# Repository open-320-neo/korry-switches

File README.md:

# Korry Switches

These are multi language docs in PDF form:

[English Documentation](https://korry.open320neo.ch/documentation-en.pdf)
[German Documentation](https://korry.open320neo.ch/README.pdf)

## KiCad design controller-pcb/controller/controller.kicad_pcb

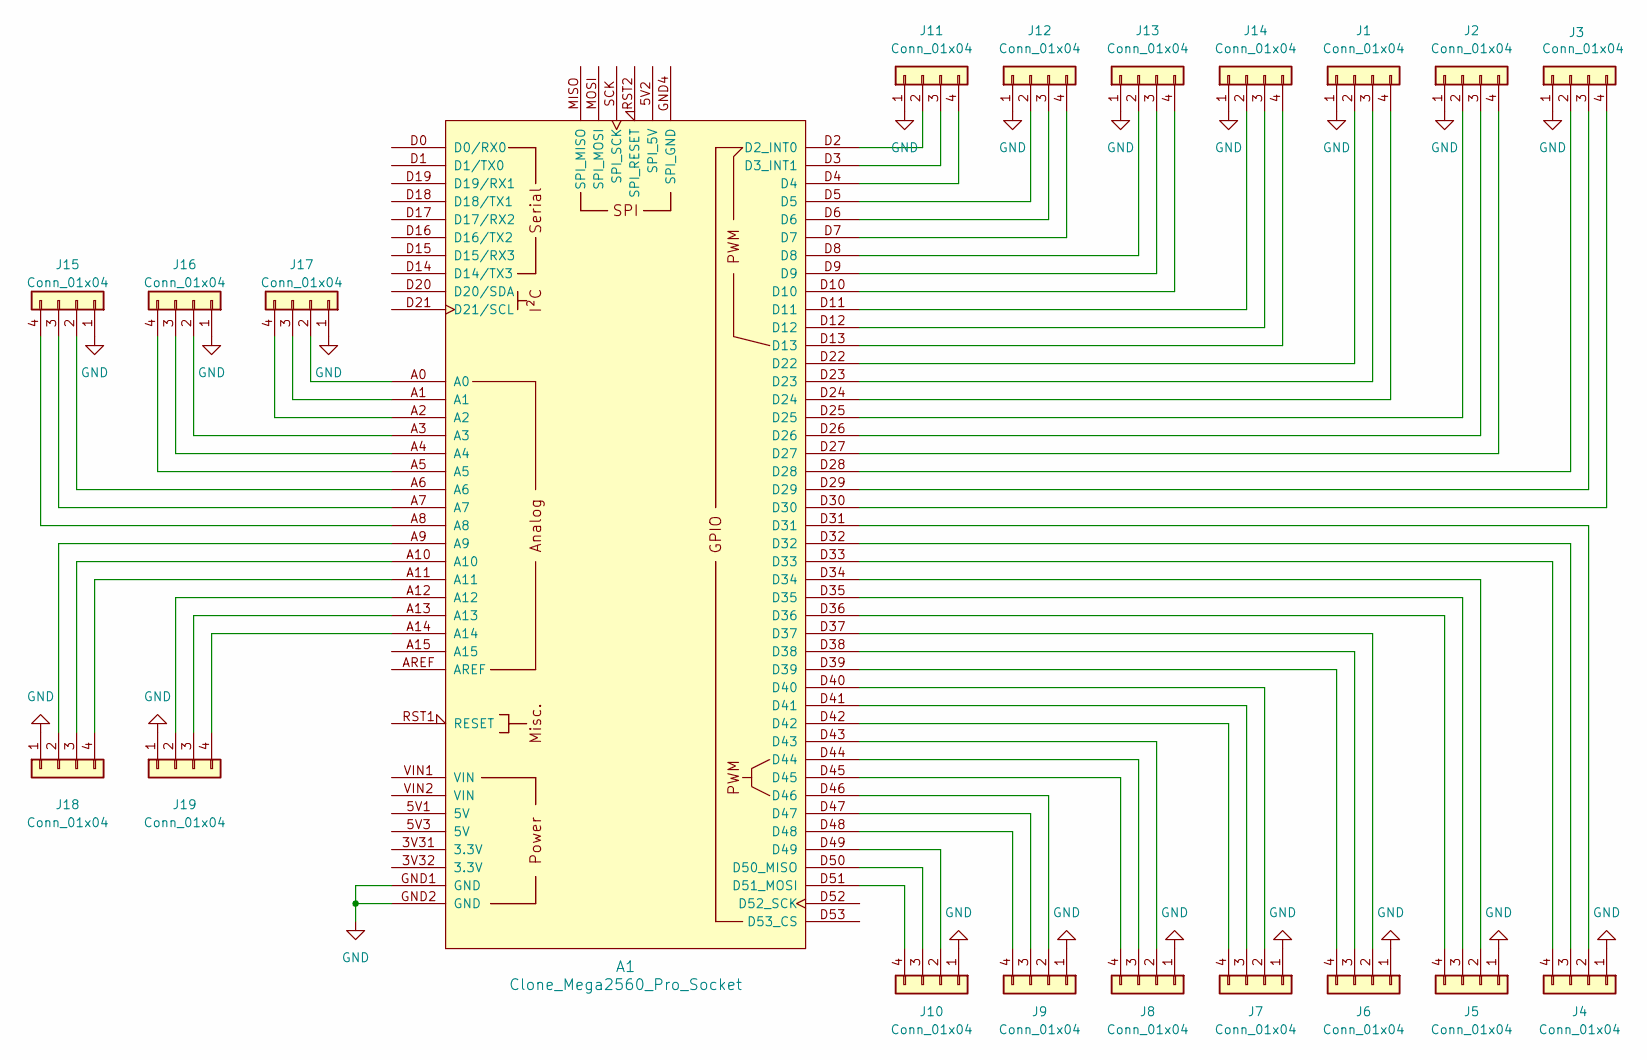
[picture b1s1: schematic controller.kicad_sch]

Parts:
A1: Clone_Mega2560_Pro_Socket
J1, J2, J3, J4, J5, J6, J7, J8, J9, J10, J11, J12, J13, J14, J15, J16, J17, J18, J19: Conn_01x04; JST_ZH_B4B-ZR_1x04_P1.50mm_Vertical

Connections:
GND: A1.GND1 (GND), A1.GND2 (GND), J1.1, J2.1, J3.1, J4.1, J5.1, J6.1, J7.1, J8.1, J9.1, J10.1, J11.1, J12.1, J13.1, J14.1, J15.1, J16.1, J17.1, J18.1, J19.1
unnamed: A1.D2 (D2_INT0), J11.2
unnamed: A1.D3 (D3_INT1), J11.3
unnamed: A1.D50 (D50_MISO), J10.3
unnamed: A1.D51 (D51_MOSI), J10.4
unnamed: A1.D22, J1.2
unnamed: A1.D23, J1.3
unnamed: A1.D24, J1.4
unnamed: A1.D25, J2.2
unnamed: A1.D26, J2.3
unnamed: A1.D27, J2.4
unnamed: A1.D28, J3.2
unnamed: A1.D29, J3.3
unnamed: A1.D30, J3.4
unnamed: A1.D31, J4.2
unnamed: A1.D32, J4.3
unnamed: A1.D33, J4.4
unnamed: A1.D34, J5.2
unnamed: A1.D35, J5.3
unnamed: A1.D36, J5.4
unnamed: A1.D37, J6.2
unnamed: A1.D38, J6.3
unnamed: A1.D39, J6.4
unnamed: A1.D40, J7.2
unnamed: A1.D41, J7.3
unnamed: A1.D42, J7.4
unnamed: A1.D43, J8.2
unnamed: A1.D44, J8.3
unnamed: A1.D45, J8.4
unnamed: A1.D46, J9.2
unnamed: A1.D47, J9.3
unnamed: A1.D48, J9.4
unnamed: A1.D49, J10.2
unnamed: A1.D4, J11.4
unnamed: A1.D5, J12.2
unnamed: A1.D6, J12.3
unnamed: A1.D7, J12.4
unnamed: A1.D8, J13.2
unnamed: A1.D9, J13.3
unnamed: A1.D10, J13.4
unnamed: A1.D11, J14.2
unnamed: A1.D12, J14.3
unnamed: A1.D13, J14.4
unnamed: A1.A6, J15.2
unnamed: A1.A7, J15.3
unnamed: A1.A8, J15.4
unnamed: A1.A3, J16.2
unnamed: A1.A4, J16.3
unnamed: A1.A5, J16.4
unnamed: A1.A0, J17.2
unnamed: A1.A1, J17.3
unnamed: A1.A2, J17.4
unnamed: A1.A9, J18.2
unnamed: A1.A10, J18.3
unnamed: A1.A11, J18.4
unnamed: A1.A12, J19.2
unnamed: A1.A13, J19.3
unnamed: A1.A14, J19.4

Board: 2 copper layers, 20 parts (0 on the bottom side), 58 nets, no tracks yet.

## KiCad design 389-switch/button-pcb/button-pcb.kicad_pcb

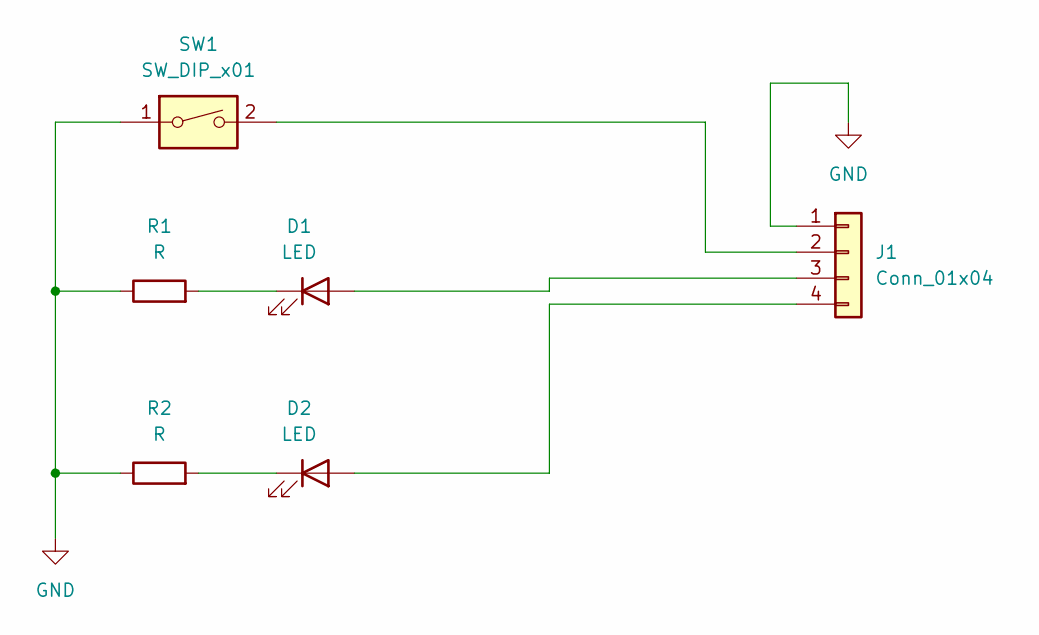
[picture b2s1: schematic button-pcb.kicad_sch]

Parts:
D1, D2: LED; LED_D3.0mm
J1: Conn_01x04; JST_ZH_B4B-ZR_1x04_P1.50mm_Vertical
R1, R2: R; R_Axial_DIN0207_L6.3mm_D2.5mm_P2.54mm_Vertical
SW1: SW_DIP_x01; button-6mm-small

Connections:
GND: J1.1, R1.1, R2.1, SW1.1
unnamed: D1.2 (A), J1.3
unnamed: D1.1 (K), R1.2
unnamed: D2.2 (A), J1.4
unnamed: D2.1 (K), R2.2
unnamed: J1.2, SW1.2

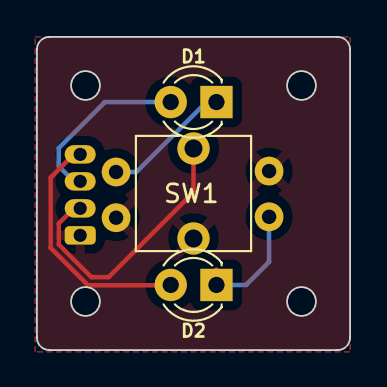
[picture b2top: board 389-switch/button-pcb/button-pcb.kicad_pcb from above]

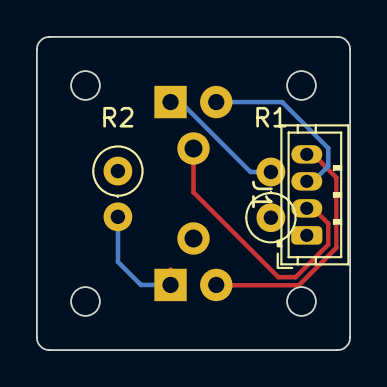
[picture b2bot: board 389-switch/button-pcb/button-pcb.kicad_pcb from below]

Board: 2 copper layers, 17.4 x 17.4 mm, 6 parts (3 on the bottom side), 6 nets.

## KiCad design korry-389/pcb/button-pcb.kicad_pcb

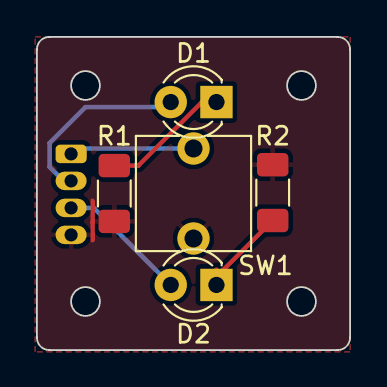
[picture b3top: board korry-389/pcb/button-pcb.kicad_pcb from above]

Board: 2 copper layers, 17.4 x 17.4 mm, 6 parts (1 on the bottom side), 6 nets.

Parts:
D1, D2: LED; LED_D3.0mm
J1: Conn_01x04; JST_ZH_B4B-ZR_1x04_P1.50mm_Vertical
R1, R2: R; R_1206_3216Metric_Pad1.30x1.75mm_HandSolder
SW1: SW_DIP_x01; button-6mm-small

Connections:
GND: J1.4, R1.1, R2.1, SW1.1
unnamed: D1.2 (A), J1.2
unnamed: D1.1 (K), R1.2
unnamed: D2.2 (A), J1.3
unnamed: D2.1 (K), R2.2
unnamed: J1.1, SW1.2

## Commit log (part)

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2024-10-30 adding license
2024-10-30 adding gitignore for nextcloud
2024-10-30 adding scad file
2024-10-30 adding kicad project
2024-10-30 adding index.md
2024-11-20 translating the readme
2025-05-02 adding 3D files of current batch
2025-05-02 updating build_docs.yml
2025-05-02 extending startup time of libretranslate
2025-05-02 removing translation
2025-05-02 deploying docs via pages
2025-05-02 adding pdf filter
2025-05-02 uploading whole docs folder
2025-05-02 renaming artefacts
2025-05-02 testing translation
2025-05-02 changing translation provider
2025-05-02 trying pdf input for translation
2025-05-02 concating all md files
2025-05-02 printing german docs to file
2025-05-02 adding lens
2025-05-02 changing the language
2025-05-02 spelling
2025-05-02 restructuring the sentence
2025-05-02 correcting
2025-05-02 changing back to google
2025-05-05 changing filename of exported docs
2025-05-07 Update LICENSE
2025-05-28 changing pcb and creating gerber files
2025-05-28 creating new project for korry switch controller
2025-07-10 adding controller board pcb
2025-07-12 preparing for Production
2025-09-09 testing
2026-02-10 removing auto translation
2026-02-10 updating file selectors
2026-02-10 updating readmes
2026-03-11 adding more german documentation
2026-03-18 cleaning up data
2026-03-18 Revert "cleaning up data"
    This reverts commit 15c657068ddfbee86325a78b1c3589183bd3c978.
2026-03-18 adding documentation about controller
